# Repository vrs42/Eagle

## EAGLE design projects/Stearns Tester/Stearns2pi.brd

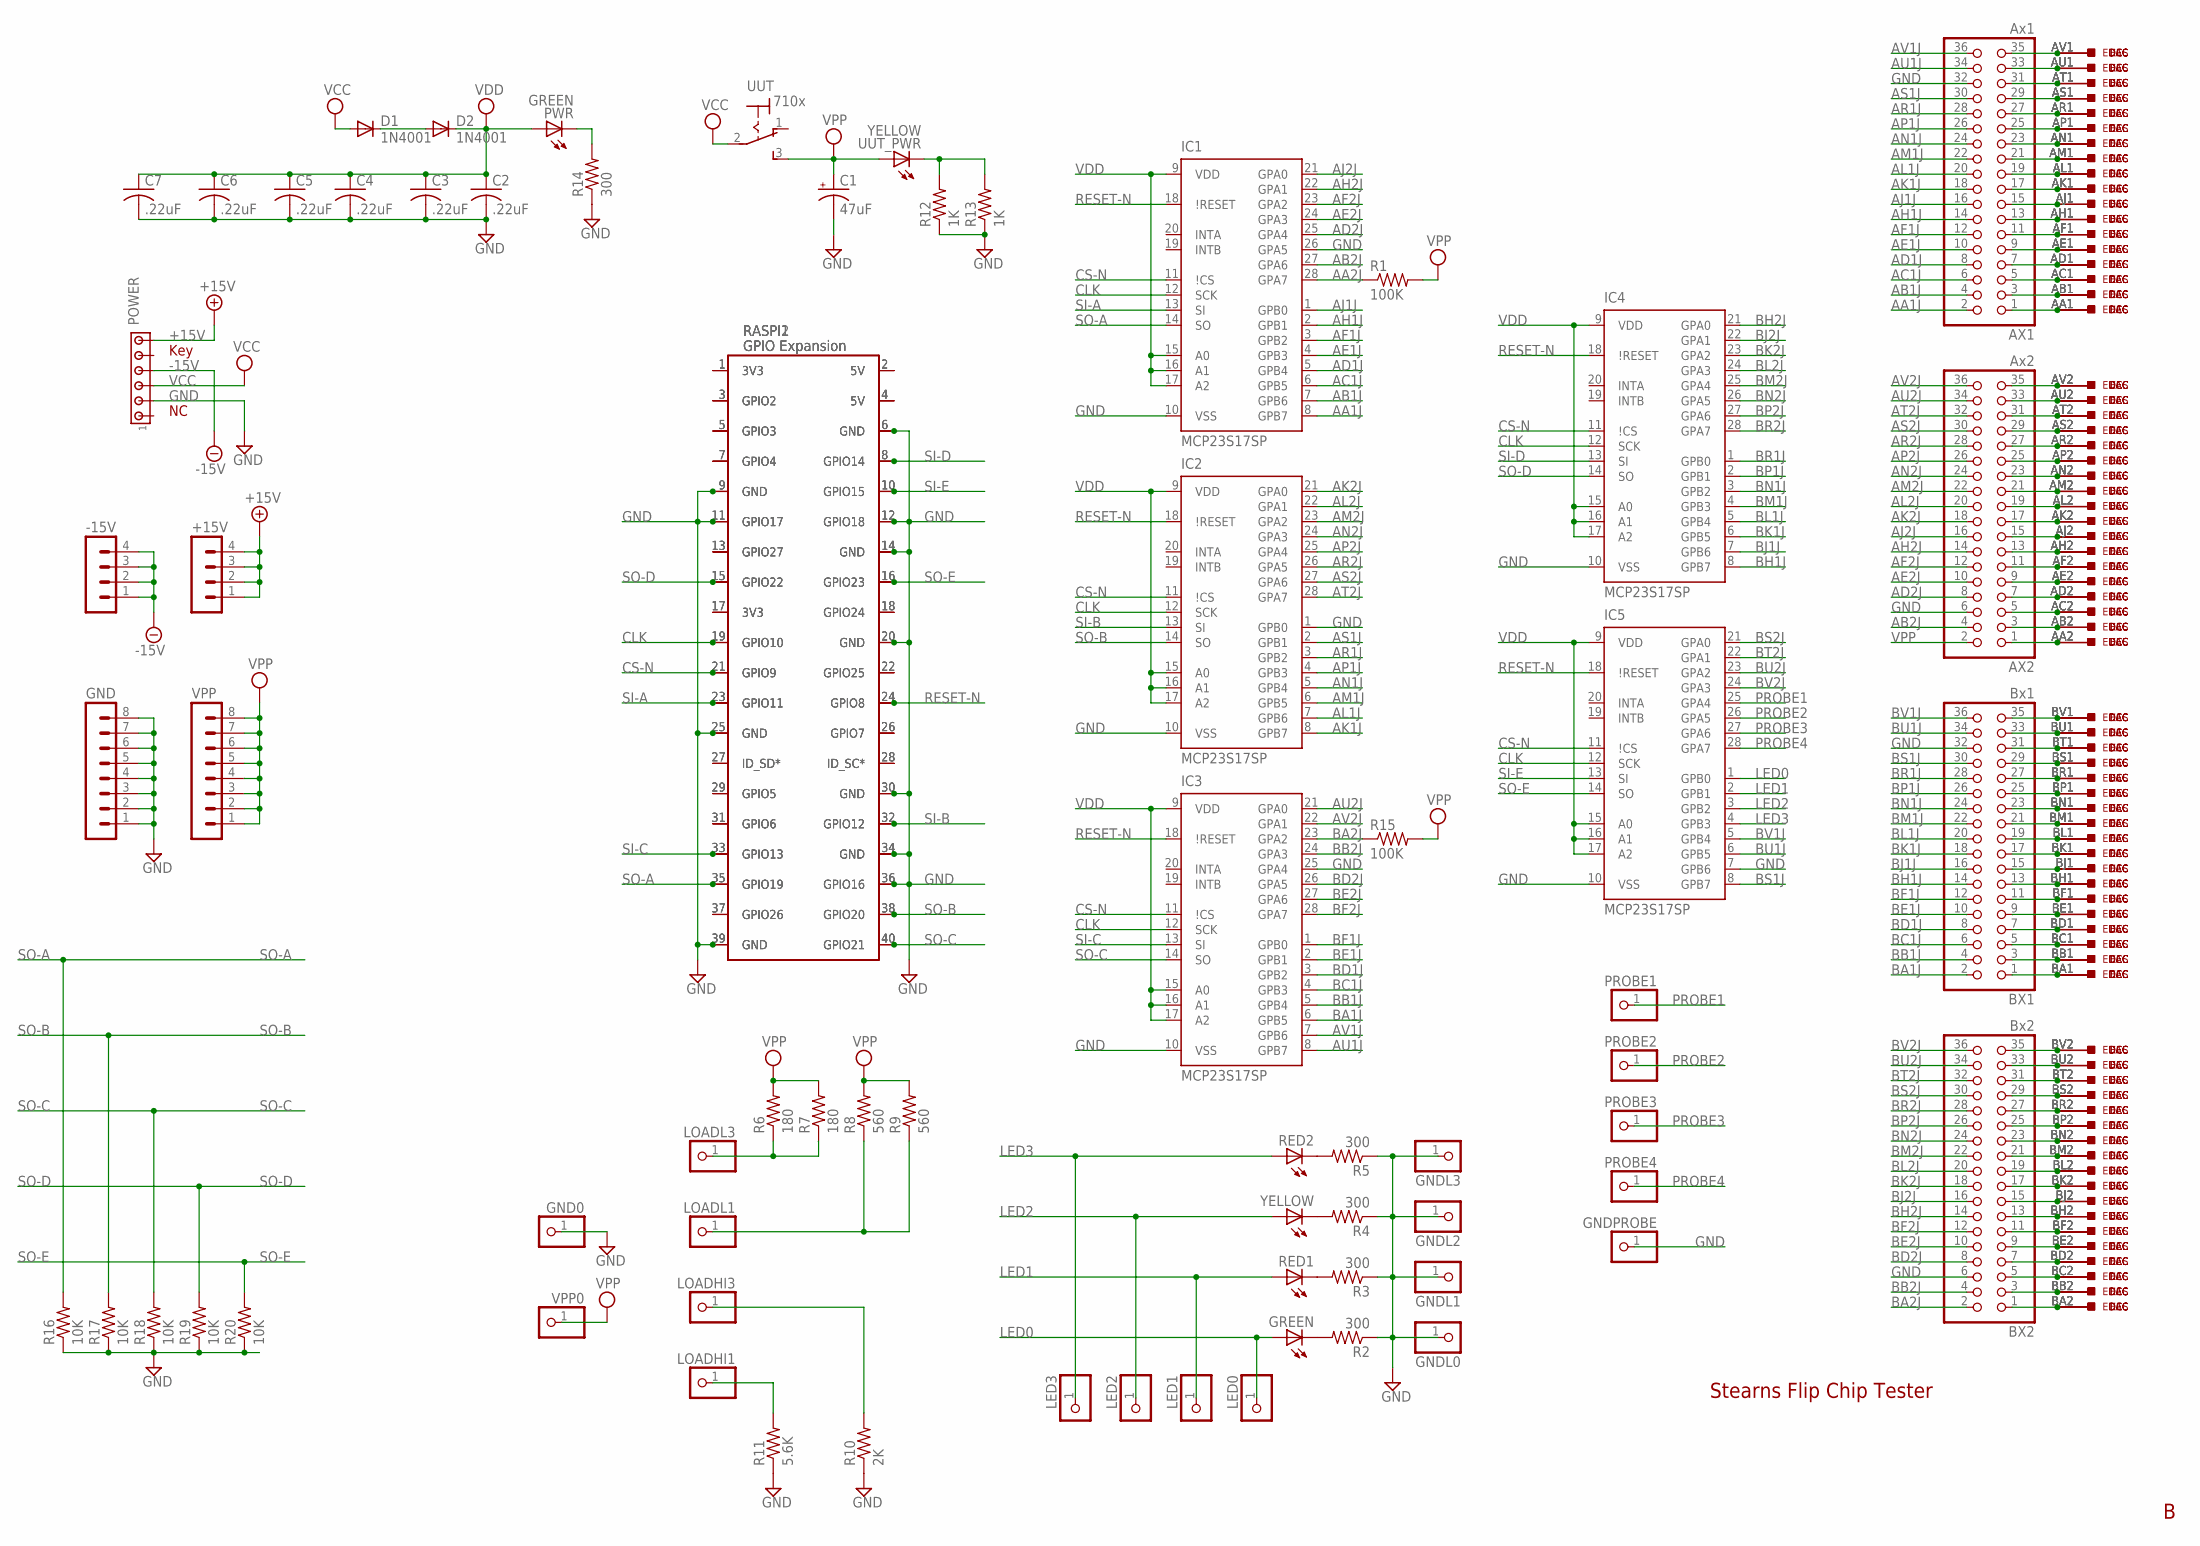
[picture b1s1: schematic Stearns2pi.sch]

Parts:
+15V: MA04-1
-15V: MA04-1
AX1: Ax1; 2X18
AX2: Ax2; 2X18
BX1: Bx1; 2X18
BX2: Bx2; 2X18
C1: 47uF; E5-8,5
C2, C3, C4, C5, C6, C7: .22uF; C050-025X075
D1, D2: 1N4001; DO41-10
DEC: W971; H807-2
ECS: W971ECS; ECS2418-2
EDAC: W971EDAC; EDAC346-36-2
GND: MA08-1
GND0: PINHD-1X1; 1X01
GNDL0, GNDL1, GNDL2, GNDL3: PINHD-1X1; 1X01
GNDPROBE: PINHD-1X1; 1X01
GREEN: LED5MM
IC1, IC2, IC3, IC4, IC5: MCP23S17SP; DIL28-3
LED0, LED1, LED2, LED3: PINHD-1X1; 1X01
LOADHI1, LOADHI3: PINHD-1X1; 1X01
LOADL1, LOADL3: PINHD-1X1; 1X01
POWER: MTA06-156; 1X6MTA
PROBE1, PROBE2, PROBE3, PROBE4: PINHD-1X1; 1X01
PWR: GREEN; LED5MM
R1, R15: 100K; 0207/10
R2, R3, R4, R5, R14: 300; 0207/10
R6, R7: 180; 0207/10
R8, R9: 560; 0207/10
R10: 2K; 0207/10
R11: 5.6K; 0207/10
R12, R13: 1K; 0207/10
R16, R17, R18, R19, R20: 10K; 0207/10
RASPI1: RPI3
RASPI2: RPI0
RED1, RED2: LED5MM
UUT: 710x; 7109MD9V3
UUT_PWR: YELLOW; LED5MM
VPP: MA08-1
VPP0: PINHD-1X1; 1X01
YELLOW: LED5MM

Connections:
+15V: +15V.1, +15V.2, +15V.3, +15V.4, POWER.6
-15V: -15V.1, -15V.2, -15V.3, -15V.4, POWER.4
AA1J: AX1.2, IC1.8 (GPB7)
AA2J: IC1.28 (GPA7), R1.1
AB1J: AX1.4, IC1.7 (GPB6)
AB2J: AX2.4, IC1.27 (GPA6)
AC1J: AX1.6, IC1.6 (GPB5)
AD1J: AX1.8, IC1.5 (GPB4)
AD2J: AX2.8, IC1.25 (GPA4)
AE1J: AX1.10, IC1.4 (GPB3)
AE2J: AX2.10, IC1.24 (GPA3)
AF1J: AX1.12, IC1.3 (GPB2)
AF2J: AX2.12, IC1.23 (GPA2)
AH1J: AX1.14, IC1.2 (GPB1)
AH2J: AX2.14, IC1.22 (GPA1)
AJ1J: AX1.16, IC1.1 (GPB0)
AJ2J: AX2.16, IC1.21 (GPA0)
AK1J: AX1.18, IC2.8 (GPB7)
AK2J: AX2.18, IC2.21 (GPA0)
AL1J: AX1.20, IC2.7 (GPB6)
AL2J: AX2.20, IC2.22 (GPA1)
AM1J: AX1.22, IC2.6 (GPB5)
AM2J: AX2.22, IC2.23 (GPA2)
AN1J: AX1.24, IC2.5 (GPB4)
AN2J: AX2.24, IC2.24 (GPA3)
AP1J: AX1.26, IC2.4 (GPB3)
AP2J: AX2.26, IC2.25 (GPA4)
AR1J: AX1.28, IC2.3 (GPB2)
AR2J: AX2.28, IC2.26 (GPA5)
AS1J: AX1.30, IC2.2 (GPB1)
AS2J: AX2.30, IC2.27 (GPA6)
AT2J: AX2.32, IC2.28 (GPA7)
AU1J: AX1.34, IC3.8 (GPB7)
AU2J: AX2.34, IC3.21 (GPA0)
AV1J: AX1.36, IC3.7 (GPB6)
AV2J: AX2.36, IC3.22 (GPA1)
BA1J: BX1.2, IC3.6 (GPB5)
BA2J: BX2.2, IC3.23 (GPA2), R15.1
BB1J: BX1.4, IC3.5 (GPB4)
BB2J: BX2.4, IC3.24 (GPA3)
BC1J: BX1.6, IC3.4 (GPB3)
BD1J: BX1.8, IC3.3 (GPB2)
BD2J: BX2.8, IC3.26 (GPA5)
BE1J: BX1.10, IC3.2 (GPB1)
BE2J: BX2.10, IC3.27 (GPA6)
BF1J: BX1.12, IC3.1 (GPB0)
BF2J: BX2.12, IC3.28 (GPA7)
BH1J: BX1.14, IC4.8 (GPB7)
BH2J: BX2.14, IC4.21 (GPA0)
BJ1J: BX1.16, IC4.7 (GPB6)
BJ2J: BX2.16, IC4.22 (GPA1)
BK1J: BX1.18, IC4.6 (GPB5)
BK2J: BX2.18, IC4.23 (GPA2)
BL1J: BX1.20, IC4.5 (GPB4)
BL2J: BX2.20, IC4.24 (GPA3)
BM1J: BX1.22, IC4.4 (GPB3)
BM2J: BX2.22, IC4.25 (GPA4)
BN1J: BX1.24, IC4.3 (GPB2)
BN2J: BX2.24, IC4.26 (GPA5)
BP1J: BX1.26, IC4.2 (GPB1)
BP2J: BX2.26, IC4.27 (GPA6)
BR1J: BX1.28, IC4.1 (GPB0)
BR2J: BX2.28, IC4.28 (GPA7)
BS1J: BX1.30, IC5.8 (GPB7)
BS2J: BX2.30, IC5.21 (GPA0)
BT2J: BX2.32, IC5.22 (GPA1)
BU1J: BX1.34, IC5.6 (GPB5)
BU2J: BX2.34, IC5.23 (GPA2)
BV1J: BX1.36, IC5.5 (GPB4)
BV2J: BX2.36, IC5.24 (GPA3)
CLK: IC1.12 (SCK), IC2.12 (SCK), IC3.12 (SCK), IC4.12 (SCK), IC5.12 (SCK), RASPI1.19 (GPIO10), RASPI2.19 (GPIO10)
CS-N: IC1.11 (\!CS), IC2.11 (\!CS), IC3.11 (\!CS), IC4.11 (\!CS), IC5.11 (\!CS), RASPI1.21 (GPIO9), RASPI2.21 (GPIO9)
GND: AX1.32, AX2.6, BX1.32, BX2.6, C1.-, C2.2, C3.2, C4.2, C5.2, C6.2, C7.2, GND.1, GND.2, GND.3, GND.4, GND.5, GND.6, GND.7, GND.8, GND0.1, GNDL0.1, GNDL1.1, GNDL2.1, GNDL3.1, GNDPROBE.1, IC1.10 (VSS), IC1.26 (GPA5), IC2.1 (GPB0), IC2.10 (VSS), IC3.10 (VSS), IC3.25 (GPA4), IC4.10 (VSS), IC5.7 (GPB6), IC5.10 (VSS), POWER.2, R2.1, R3.1, R4.1, R5.1, R10.1, R11.1, R12.1, R13.1, R14.1, R16.1, R17.1, R18.1, R19.1, R20.1, RASPI1.6 (GND), RASPI1.9 (GND), RASPI1.11 (GPIO17), RASPI1.12 (GPIO18), RASPI1.14 (GND), RASPI1.20 (GND), RASPI1.25 (GND), RASPI1.30 (GND), RASPI1.34 (GND), RASPI1.36 (GPIO16), RASPI1.39 (GND), RASPI2.6 (GND), RASPI2.9 (GND), RASPI2.11 (GPIO17), RASPI2.12 (GPIO18), RASPI2.14 (GND), RASPI2.20 (GND), RASPI2.25 (GND), RASPI2.30 (GND), RASPI2.34 (GND), RASPI2.36 (GPIO16), RASPI2.39 (GND), UUT.NC@1 (GND), UUT.NC@2 (GND), UUT.NC@3 (GND), UUT.NC@4 (GND), UUT.NC@5 (GND), UUT.NC@6 (GND), UUT.NC@7 (GND), UUT.NC@8 (GND)
LED0: GREEN.A, IC5.1 (GPB0), LED0.1
LED1: IC5.2 (GPB1), LED1.1, RED1.A
LED2: IC5.3 (GPB2), LED2.1, YELLOW.A
LED3: IC5.4 (GPB3), LED3.1, RED2.A
unnamed: AX1.1, DEC.AA1, ECS.AA1, EDAC.AA1
unnamed: AX1.35, DEC.AV1, ECS.AV1, EDAC.AV1
unnamed: AX1.33, DEC.AU1, ECS.AU1, EDAC.AU1
unnamed: AX1.31, DEC.AT1, ECS.AT1, EDAC.AT1
unnamed: AX1.29, DEC.AS1, ECS.AS1, EDAC.AS1
unnamed: AX1.27, DEC.AR1, ECS.AR1, EDAC.AR1
unnamed: AX1.25, DEC.AP1, ECS.AP1, EDAC.AP1
unnamed: AX1.23, DEC.AN1, ECS.AN1, EDAC.AN1
unnamed: AX1.21, DEC.AM1, ECS.AM1, EDAC.AM1
unnamed: AX1.19, DEC.AL1, ECS.AL1, EDAC.AL1
unnamed: AX1.17, DEC.AK1, ECS.AK1, EDAC.AK1
unnamed: AX1.15, DEC.AJ1, ECS.AJ1, EDAC.AJ1
unnamed: AX1.13, DEC.AH1, ECS.AH1, EDAC.AH1
unnamed: AX1.11, DEC.AF1, ECS.AF1, EDAC.AF1
unnamed: AX1.9, DEC.AE1, ECS.AE1, EDAC.AE1
unnamed: AX1.7, DEC.AD1, ECS.AD1, EDAC.AD1
unnamed: AX1.5, DEC.AC1, ECS.AC1, EDAC.AC1
unnamed: AX1.3, DEC.AB1, ECS.AB1, EDAC.AB1
unnamed: AX2.1, DEC.AA2, ECS.AA2, EDAC.AA2
unnamed: AX2.3, DEC.AB2, ECS.AB2, EDAC.AB2
unnamed: AX2.5, DEC.AC2, ECS.AC2, EDAC.AC2
unnamed: AX2.7, DEC.AD2, ECS.AD2, EDAC.AD2
unnamed: AX2.9, DEC.AE2, ECS.AE2, EDAC.AE2
unnamed: AX2.11, DEC.AF2, ECS.AF2, EDAC.AF2
unnamed: AX2.13, DEC.AH2, ECS.AH2, EDAC.AH2
unnamed: AX2.15, DEC.AJ2, ECS.AJ2, EDAC.AJ2
unnamed: AX2.17, DEC.AK2, ECS.AK2, EDAC.AK2
unnamed: AX2.19, DEC.AL2, ECS.AL2, EDAC.AL2
unnamed: AX2.21, DEC.AM2, ECS.AM2, EDAC.AM2
unnamed: AX2.23, DEC.AN2, ECS.AN2, EDAC.AN2
unnamed: AX2.25, DEC.AP2, ECS.AP2, EDAC.AP2
unnamed: AX2.27, DEC.AR2, ECS.AR2, EDAC.AR2
unnamed: AX2.29, DEC.AS2, ECS.AS2, EDAC.AS2
unnamed: AX2.31, DEC.AT2, ECS.AT2, EDAC.AT2
unnamed: AX2.33, DEC.AU2, ECS.AU2, EDAC.AU2
unnamed: AX2.35, DEC.AV2, ECS.AV2, EDAC.AV2
unnamed: BX2.1, DEC.BA2, ECS.BA2, EDAC.BA2
unnamed: BX2.3, DEC.BB2, ECS.BB2, EDAC.BB2
unnamed: BX2.5, DEC.BC2, ECS.BC2, EDAC.BC2
unnamed: BX2.7, DEC.BD2, ECS.BD2, EDAC.BD2
unnamed: BX2.9, DEC.BE2, ECS.BE2, EDAC.BE2
unnamed: BX2.11, DEC.BF2, ECS.BF2, EDAC.BF2
unnamed: BX2.13, DEC.BH2, ECS.BH2, EDAC.BH2
unnamed: BX2.15, DEC.BJ2, ECS.BJ2, EDAC.BJ2
unnamed: BX2.17, DEC.BK2, ECS.BK2, EDAC.BK2
unnamed: BX2.19, DEC.BL2, ECS.BL2, EDAC.BL2
unnamed: BX2.21, DEC.BM2, ECS.BM2, EDAC.BM2
unnamed: BX2.23, DEC.BN2, ECS.BN2, EDAC.BN2
unnamed: BX2.25, DEC.BP2, ECS.BP2, EDAC.BP2
unnamed: BX2.27, DEC.BR2, ECS.BR2, EDAC.BR2
unnamed: BX2.29, DEC.BS2, ECS.BS2, EDAC.BS2
unnamed: BX2.31, DEC.BT2, ECS.BT2, EDAC.BT2
unnamed: BX2.33, DEC.BU2, ECS.BU2, EDAC.BU2
unnamed: BX2.35, DEC.BV2, ECS.BV2, EDAC.BV2
unnamed: BX1.1, DEC.BA1, ECS.BA1, EDAC.BA1
unnamed: BX1.3, DEC.BB1, ECS.BB1, EDAC.BB1
unnamed: BX1.5, DEC.BC1, ECS.BC1, EDAC.BC1
unnamed: BX1.7, DEC.BD1, ECS.BD1, EDAC.BD1
unnamed: BX1.9, DEC.BE1, ECS.BE1, EDAC.BE1
unnamed: BX1.11, DEC.BF1, ECS.BF1, EDAC.BF1
unnamed: BX1.13, DEC.BH1, ECS.BH1, EDAC.BH1
unnamed: BX1.15, DEC.BJ1, ECS.BJ1, EDAC.BJ1
unnamed: BX1.17, DEC.BK1, ECS.BK1, EDAC.BK1
unnamed: BX1.19, DEC.BL1, ECS.BL1, EDAC.BL1
unnamed: BX1.21, DEC.BM1, ECS.BM1, EDAC.BM1
unnamed: BX1.23, DEC.BN1, ECS.BN1, EDAC.BN1
unnamed: BX1.25, DEC.BP1, ECS.BP1, EDAC.BP1
unnamed: BX1.27, DEC.BR1, ECS.BR1, EDAC.BR1
unnamed: BX1.29, DEC.BS1, ECS.BS1, EDAC.BS1
unnamed: BX1.31, DEC.BT1, ECS.BT1, EDAC.BT1
unnamed: BX1.33, DEC.BU1, ECS.BU1, EDAC.BU1
unnamed: BX1.35, DEC.BV1, ECS.BV1, EDAC.BV1
unnamed: GREEN.K (C), R2.2
unnamed: R3.2, RED1.K (C)
unnamed: R4.2, YELLOW.K (C)
unnamed: R5.2, RED2.K (C)
unnamed: LOADL3.1, R6.1, R7.1
unnamed: LOADL1.1, R8.1, R9.1
unnamed: LOADHI1.1, R11.2
unnamed: LOADHI3.1, R10.2
unnamed: D1.C, D2.A
unnamed: R12.2, R13.2, UUT_PWR.K (C)
unnamed: PWR.K (C), R14.2
unnamed: RASPI1.1 (3V3), RASPI2.1 (3V3)
unnamed: RASPI1.2 (5V), RASPI2.2 (5V)
unnamed: RASPI1.3 (GPIO2), RASPI2.3 (GPIO2)
unnamed: RASPI1.4 (5V), RASPI2.4 (5V)
unnamed: RASPI1.5 (GPIO3), RASPI2.5 (GPIO3)
unnamed: RASPI1.7 (GPIO4), RASPI2.7 (GPIO4)
unnamed: RASPI1.13 (GPIO27), RASPI2.13 (GPIO27)
unnamed: RASPI1.17 (3V3), RASPI2.17 (3V3)
unnamed: RASPI1.18 (GPIO24), RASPI2.18 (GPIO24)
unnamed: RASPI1.22 (GPIO25), RASPI2.22 (GPIO25)
unnamed: RASPI1.26 (GPIO7), RASPI2.26 (GPIO7)
unnamed: RASPI1.27 (ID_SD*), RASPI2.27 (ID_SD*)
unnamed: RASPI1.28 (ID_SC*), RASPI2.28 (ID_SC*)
unnamed: RASPI1.29 (GPIO5), RASPI2.29 (GPIO5)
unnamed: RASPI1.31 (GPIO6), RASPI2.31 (GPIO6)
unnamed: RASPI1.37 (GPIO26), RASPI2.37 (GPIO26)
PROBE1: IC5.25 (GPA4), PROBE1.1
PROBE2: IC5.26 (GPA5), PROBE2.1
PROBE3: IC5.27 (GPA6), PROBE3.1
PROBE4: IC5.28 (GPA7), PROBE4.1
RESET-N: IC1.18 (\!RESET), IC2.18 (\!RESET), IC3.18 (\!RESET), IC4.18 (\!RESET), IC5.18 (\!RESET), RASPI1.24 (GPIO8), RASPI2.24 (GPIO8)
SI-A: IC1.13 (SI), RASPI1.23 (GPIO11), RASPI2.23 (GPIO11)
SI-B: IC2.13 (SI), RASPI1.32 (GPIO12), RASPI2.32 (GPIO12)
SI-C: IC3.13 (SI), RASPI1.33 (GPIO13), RASPI2.33 (GPIO13)
SI-D: IC4.13 (SI), RASPI1.8 (GPIO14), RASPI2.8 (GPIO14)
SI-E: IC5.13 (SI), RASPI1.10 (GPIO15), RASPI2.10 (GPIO15)
SO-A: IC1.14 (SO), R16.2, RASPI1.35 (GPIO19), RASPI2.35 (GPIO19)
SO-B: IC2.14 (SO), R17.2, RASPI1.38 (GPIO20), RASPI2.38 (GPIO20)
SO-C: IC3.14 (SO), R18.2, RASPI1.40 (GPIO21), RASPI2.40 (GPIO21)
SO-D: IC4.14 (SO), R19.2, RASPI1.15 (GPIO22), RASPI2.15 (GPIO22)
SO-E: IC5.14 (SO), R20.2, RASPI1.16 (GPIO23), RASPI2.16 (GPIO23)
VCC: D1.A, POWER.3, UUT.2
VDD: C2.1, C3.1, C4.1, C5.1, C6.1, C7.1, D2.C, IC1.9 (VDD), IC1.15 (A0), IC1.16 (A1), IC1.17 (A2), IC2.9 (VDD), IC2.15 (A0), IC2.16 (A1), IC2.17 (A2), IC3.9 (VDD), IC3.15 (A0), IC3.16 (A1), IC3.17 (A2), IC4.9 (VDD), IC4.15 (A0), IC4.16 (A1), IC4.17 (A2), IC5.9 (VDD), IC5.15 (A0), IC5.16 (A1), IC5.17 (A2), PWR.A
VPP: AX2.2, C1.+, R1.2, R6.2, R7.2, R8.2, R9.2, R15.2, UUT.3 (S), UUT_PWR.A, VPP.1, VPP.2, VPP.3, VPP.4, VPP.5, VPP.6, VPP.7, VPP.8, VPP0.1

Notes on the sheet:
Stearns Flip Chip Tester
Key

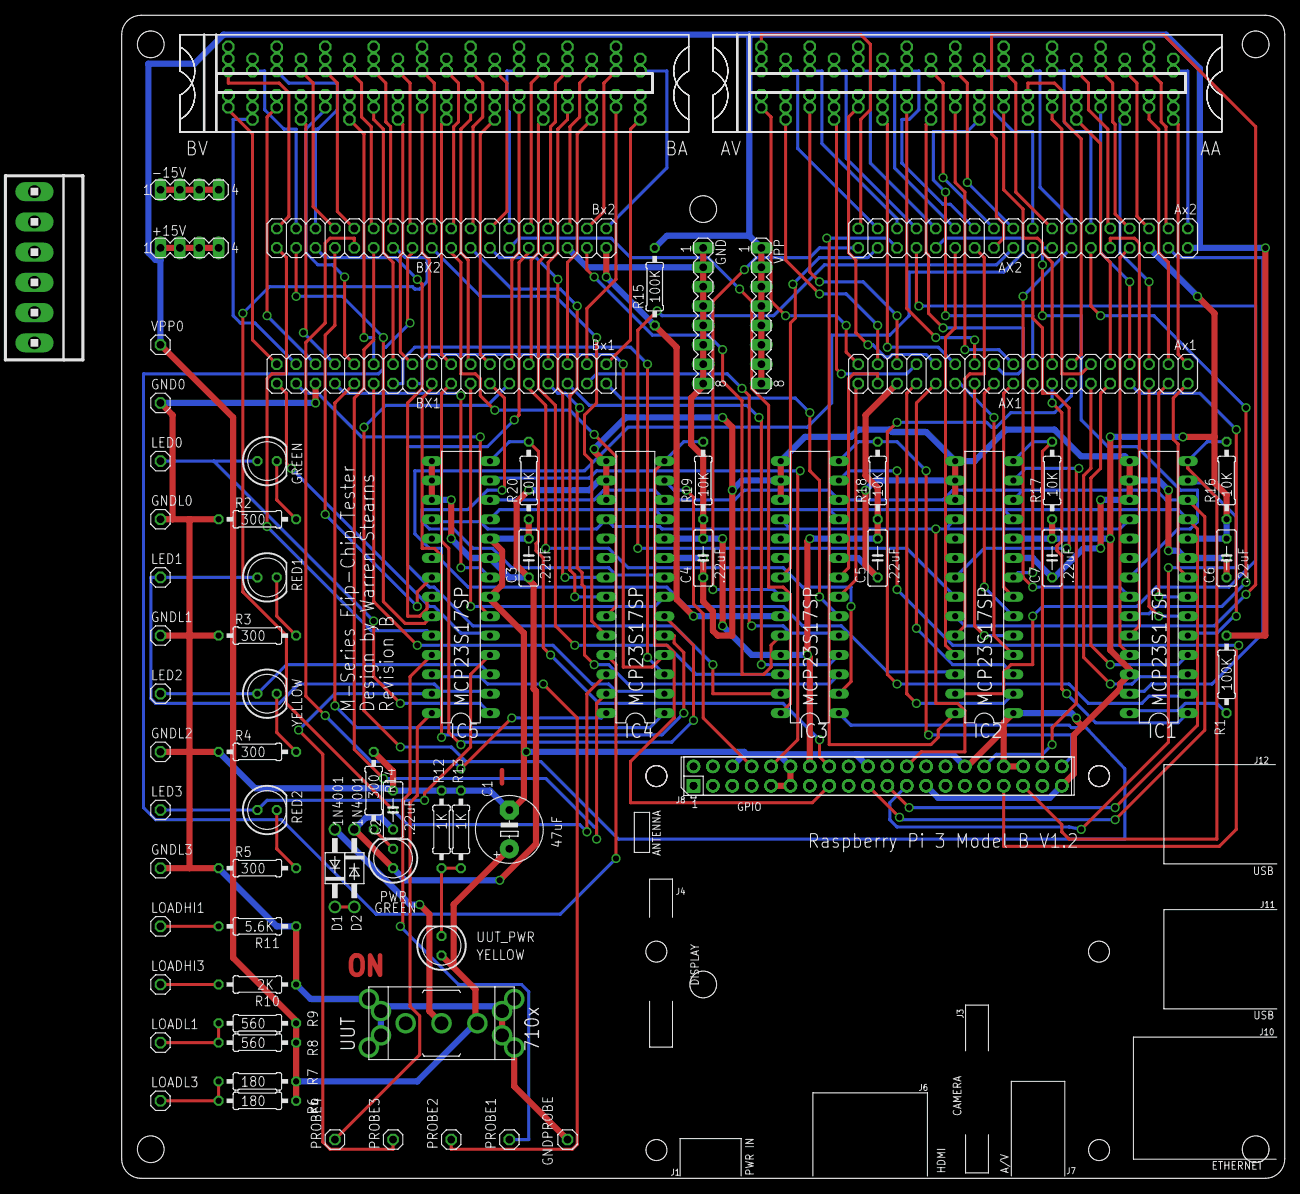
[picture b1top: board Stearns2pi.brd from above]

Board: 2 copper layers, 152.4 x 152.4 mm, 74 parts (0 on the bottom side), 194 nets.

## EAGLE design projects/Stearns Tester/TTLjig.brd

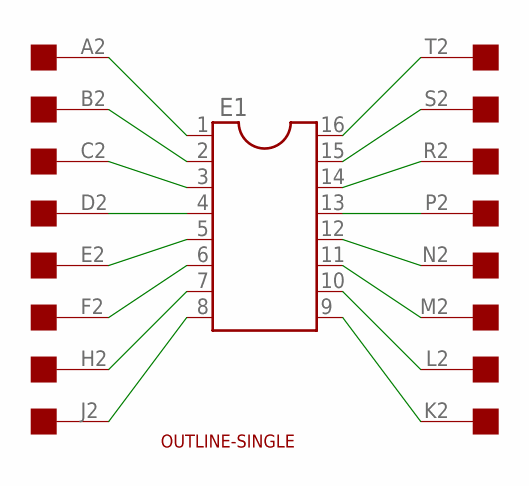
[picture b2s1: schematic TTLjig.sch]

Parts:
E1: DIL16
U$1: OUTLINE-SINGLE; SINGLE
U$2: EDGE-1; EDGE-CON1

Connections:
unnamed: E1.8, U$2.J2
unnamed: E1.1, U$2.A2
unnamed: E1.13, U$2.P2
unnamed: E1.7, U$2.H2
unnamed: E1.6, U$2.F2
unnamed: E1.5, U$2.E2
unnamed: E1.4, U$2.D2
unnamed: E1.3, U$2.C2
unnamed: E1.2, U$2.B2
unnamed: E1.16, U$2.T2
unnamed: E1.15, U$2.S2
unnamed: E1.14, U$2.R2
unnamed: E1.9, U$2.K2
unnamed: E1.10, U$2.L2
unnamed: E1.11, U$2.M2
unnamed: E1.12, U$2.N2

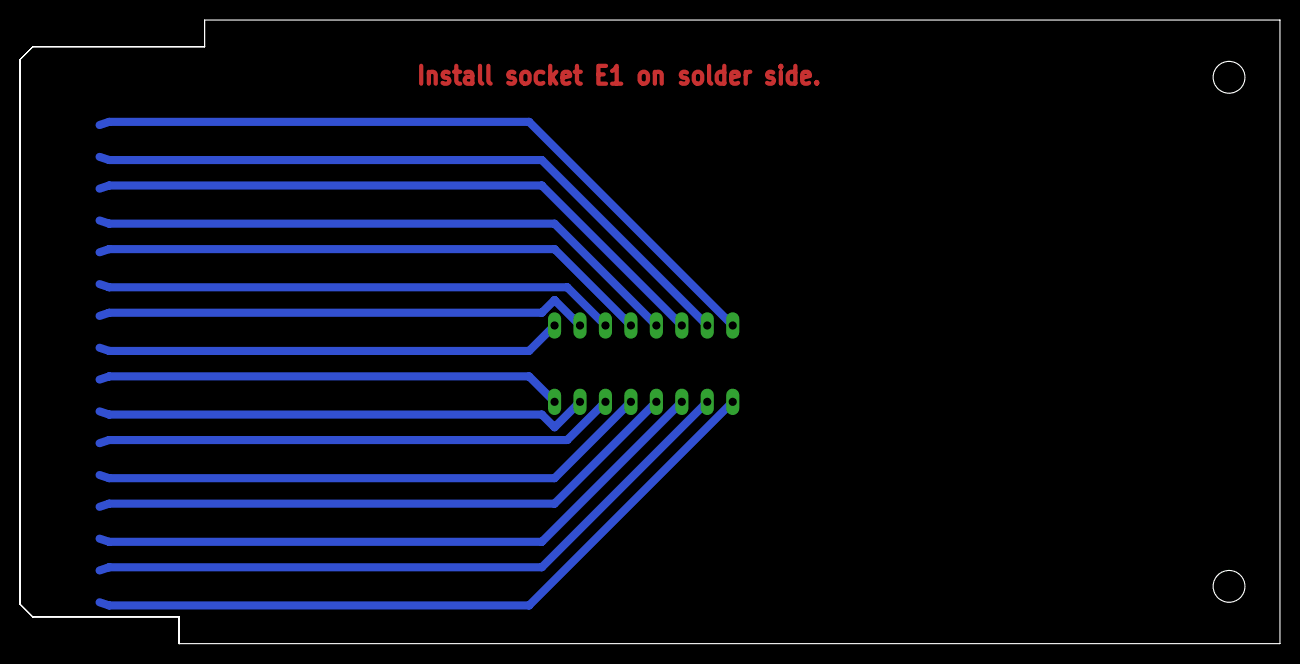
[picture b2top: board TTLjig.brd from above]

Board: 2 copper layers, 125.7 x 62.2 mm, 3 parts (1 on the bottom side), 16 nets.
